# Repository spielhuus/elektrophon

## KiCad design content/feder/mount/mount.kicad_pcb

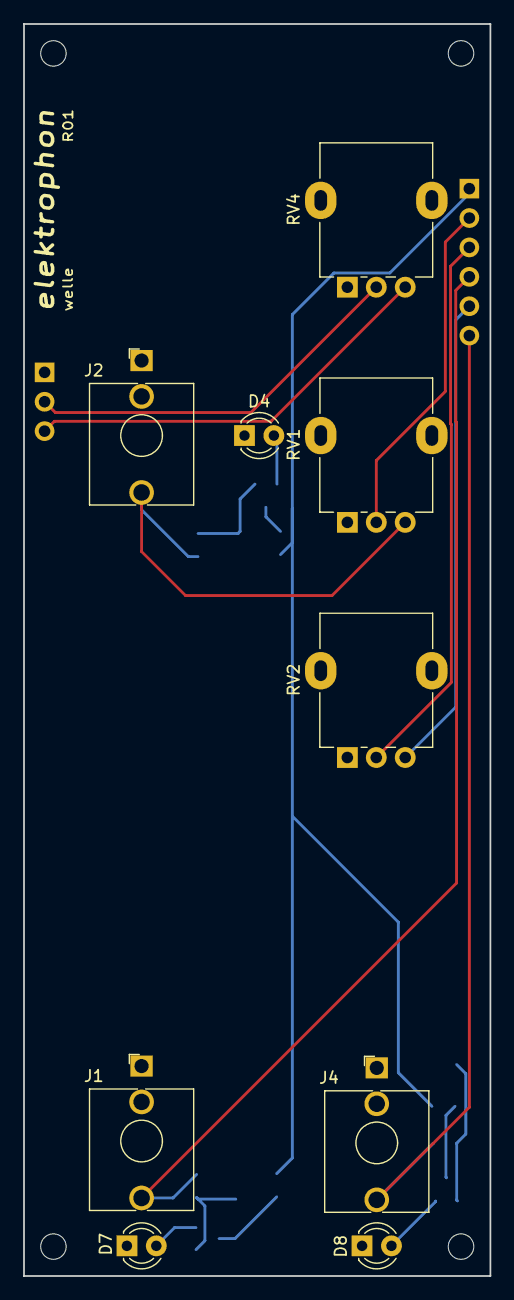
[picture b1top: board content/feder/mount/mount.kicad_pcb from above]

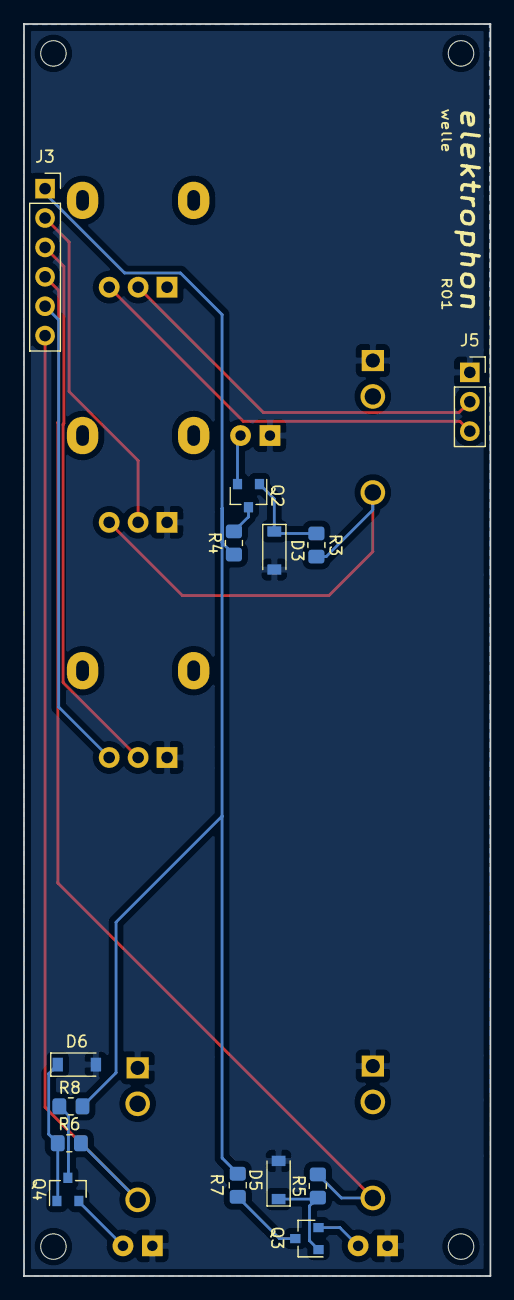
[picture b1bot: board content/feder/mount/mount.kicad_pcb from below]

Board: 2 copper layers, 40.3 x 108.2 mm, 27 parts (14 on the bottom side), 19 nets.

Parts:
D3, D5, D6: 1N4148W; D_SOD-123
D4: LED (Yellow); LED_D3.0mm
D7: LED (Green); LED_D3.0mm
D8: LED (Red); LED_D3.0mm
H1, H2, H3, H4: MountingHole; MountingHole_2.2mm_M2
J1: INPUT; Jack_3.5mm_WQP-PJ398SM_Vertical
J2: Control; Jack_3.5mm_WQP-PJ398SM_Vertical
J3: Conn_01x06_Male; PinSocket_1x06_P2.54mm_Vertical
J4: OUT; Jack_3.5mm_WQP-PJ398SM_Vertical
J5: Conn_01x03_Male; PinSocket_1x03_P2.54mm_Vertical
Q2, Q3, Q4: MMBT3904; SOT-23
R3, R5, R6: 100k; R_0805_2012Metric_Pad1.20x1.40mm_HandSolder
R4, R7, R8: 5k; R_0805_2012Metric_Pad1.20x1.40mm_HandSolder
RV1, RV2: 100k; Potentiometer_Alpha_RD901F-40-00D_Single_Vertical
RV4: 47k; Potentiometer_Alpha_RD901F-40-00D_Single_Vertical

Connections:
+5V: J3.1, R4.1, R7.1, R8.1
+15V: J3.5, RV2.3
/control: J3.2, RV1.2
/control_in: J2.T, R3.2, RV1.3
/input: J1.T, J3.4, R5.2
/out: J3.6, J4.T, R6.2
/range: J3.3, RV2.2
/shape_a: J5.2, RV4.2
/shape_b: J5.3, RV4.3
GND: D3.2, D4.1, D5.2, D6.2, D7.1, D8.1, J1.S, J2.S, J4.S, J5.1, RV1.1, RV2.1
unnamed: D3.1, Q2.1, R3.1
unnamed: D4.2, Q2.2
unnamed: D5.1, Q3.1, R5.1
unnamed: D6.1, Q4.1, R6.1
unnamed: D7.2, Q3.2
unnamed: D8.2, Q4.2
unnamed: Q2.3, R4.2
unnamed: Q3.3, R7.2
unnamed: Q4.3, R8.2

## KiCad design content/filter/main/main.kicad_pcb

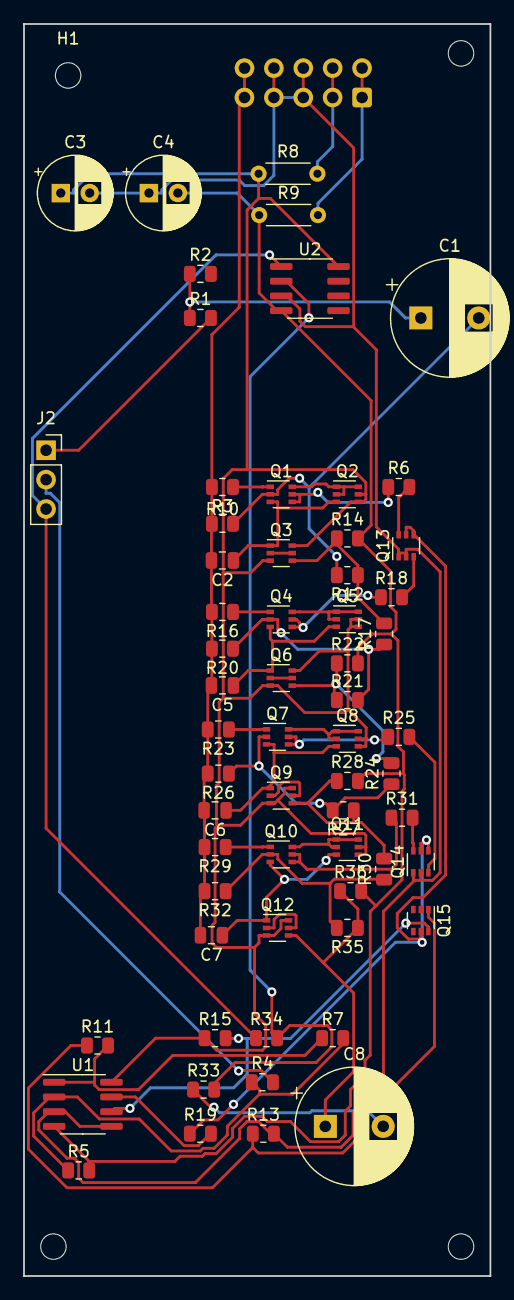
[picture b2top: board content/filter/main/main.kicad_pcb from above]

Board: 2 copper layers, 40.3 x 108.2 mm, 67 parts (1 on the bottom side), 50 nets.

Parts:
C1, C8: 10u; CP_Radial_D10.0mm_P5.00mm
C2, C5, C6, C7: 1n; C_0805_2012Metric
C3, C4: 22u; CP_Radial_D6.3mm_P2.50mm
H1, H2, H3, H4: MountingHole; MountingHole_2.2mm_M2
J1: 10 Pos; IDC-Header_2x05_P2.54mm_Vertical
J2: Conn_01x03_Female; PinSocket_1x03_P2.54mm_Vertical
Q1, Q3, Q4, Q6, Q7, Q9, Q10, Q12, Q13, Q14, Q15: DMMT3904W; SOT-363_SC-70-6
Q2, Q5, Q8, Q11: DMMT3906W; SOT-363_SC-70-6
R1, R2, R12, R14, R17, R21, R22, R24, R27, R28, R30, R33, R35, R36: 10k; R_0805_2012Metric
R3, R10, R16, R20, R23, R26, R29, R32: 220; R_0805_2012Metric
R4, R34: 100k; R_0805_2012Metric
R5: 200k; R_0805_2012Metric
R6, R13, R18, R25, R31: 1k; R_0805_2012Metric
R7: 51k; R_0805_2012Metric
R8, R9: 10; R_Axial_DIN0204_L3.6mm_D1.6mm_P5.08mm_Horizontal
R11: 27k; R_0805_2012Metric
R15: 1M; R_0805_2012Metric
R19: 2.2k; R_0805_2012Metric
U1, U2: TL072; SOIC-8_3.9x4.9mm_P1.27mm

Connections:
+5V: C2.2, C5.2, C6.2, C7.2, J1.9, J1.10, R3.2, R10.2, R16.2, R20.2, R23.2, R26.2, R29.2, R32.2
+15V: C3.1, Q2.4, Q2.5, Q3.3, Q3.6, Q5.4, Q5.5, Q6.3, Q6.6, Q8.4, Q8.5, Q9.3, Q9.6, Q11.4, Q11.5, Q12.3, Q12.6, R8.1, R15.1, U1.8, U2.8
-15V: C4.2, R5.2, R9.1, R14.2, R22.2, R28.2, R36.2, U1.4, U2.4
/CV: J2.2, R4.2
/IN: J2.1, R1.2
/OUT: J2.3, R34.1, U2.1
GND: C3.2, C4.1, J1.5, J1.6, J1.7, J1.8, Q13.1, Q13.2, Q14.1, Q14.2, R13.2, U1.3, U1.5, U2.3
unnamed: C1.1, R1.1, R2.1
unnamed: C1.2, Q1.2, R10.1, R12.2
unnamed: C2.1, Q1.3, Q2.3, Q3.1
unnamed: C5.1, Q4.3, Q5.3, Q6.1
unnamed: C6.1, Q7.3, Q8.3, Q9.1
unnamed: C7.1, Q10.3, Q11.3, Q12.1
unnamed: C8.1, Q12.4, R35.1, R36.1
unnamed: C8.2, R33.1
unnamed: Q1.1, R3.1
unnamed: Q1.4, Q1.5, R6.1
unnamed: Q1.6, Q2.1, Q2.2, Q2.6
unnamed: Q3.2, Q3.5
unnamed: Q3.4, R12.1, R14.1, R17.2
unnamed: Q4.1, R16.1
unnamed: Q4.2, R17.1, R20.1, R21.2
unnamed: Q4.4, Q4.5, R18.1
unnamed: Q4.6, Q5.1, Q5.2, Q5.6
unnamed: Q6.2, Q6.5
unnamed: Q6.4, R21.1, R22.1, R24.2
unnamed: Q7.1, R23.1
unnamed: Q7.2, R24.1, R26.1, R27.2
unnamed: Q7.4, Q7.5, R25.1
unnamed: Q7.6, Q8.1, Q8.2, Q8.6
unnamed: Q9.2, Q9.5
unnamed: Q9.4, R27.1, R28.1, R30.2
unnamed: Q10.1, R29.1
unnamed: Q10.2, R30.1, R32.1, R35.2
unnamed: Q10.4, Q10.5, R31.1
unnamed: Q10.6, Q11.1, Q11.2, Q11.6
unnamed: Q12.2, Q12.5
unnamed: Q13.3, R18.2
unnamed: Q13.4, Q13.5, Q14.4, Q14.5, Q15.5, R19.1
unnamed: Q13.6, R6.2
unnamed: Q14.3, R25.2
unnamed: Q14.6, R31.2
unnamed: Q15.1, R11.1, R13.1
unnamed: Q15.6, R15.2, U1.6
unnamed: R4.1, R5.1, R7.2, U1.2
unnamed: R7.1, R11.2, U1.1
unnamed: R19.2, U1.7
unnamed: R33.2, R34.2, U2.2
VN: J1.1, J1.2, R9.2
VP: J1.3, J1.4, R8.2

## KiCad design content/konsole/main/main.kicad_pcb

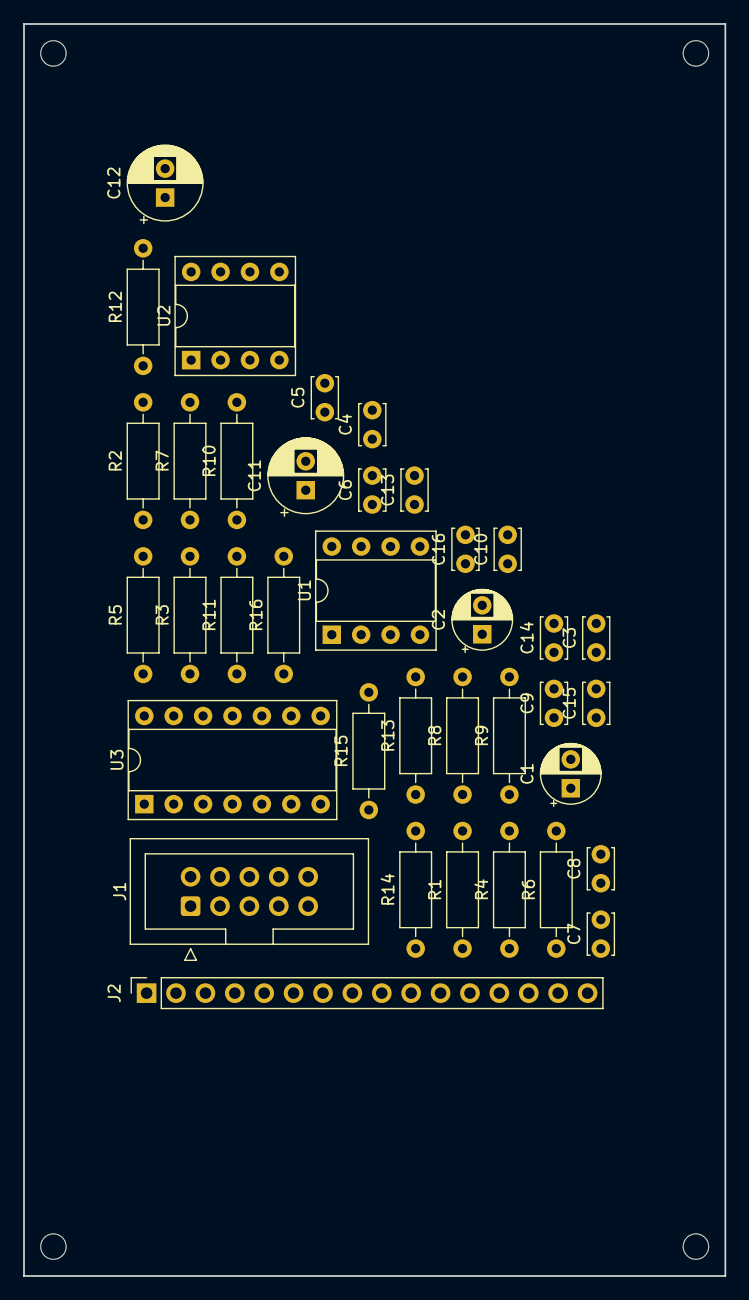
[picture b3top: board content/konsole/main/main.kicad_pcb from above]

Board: 2 copper layers, 60.6 x 108.2 mm, 41 parts (0 on the bottom side), 22 nets, no tracks yet.

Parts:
C1, C2: 10u; CP_Radial_D5.0mm_P2.50mm
C3, C4: 4u7; C_Disc_D3.4mm_W2.1mm_P2.50mm
C5, C6: 47p; C_Disc_D3.4mm_W2.1mm_P2.50mm
C7, C8, C9, C10, C13, C14, C15, C16: 0.1u; C_Disc_D3.4mm_W2.1mm_P2.50mm
C11, C12: 22u; CP_Radial_D6.3mm_P2.50mm
H1, H2, H3, H4: MountingHole; MountingHole_2.2mm_M2
J1: IDC Header; IDC-Header_2x05_P2.54mm_Vertical
J2: Conn_01x16_Female; PinSocket_1x16_P2.54mm_Vertical
R1, R2, R5, R6, R13, R14: 5k; R_Axial_DIN0207_L6.3mm_D2.5mm_P10.16mm_Horizontal
R3, R4, R9, R10, R15, R16: 10k; R_Axial_DIN0207_L6.3mm_D2.5mm_P10.16mm_Horizontal
R7, R8: 1k; R_Axial_DIN0207_L6.3mm_D2.5mm_P10.16mm_Horizontal
R11, R12: 10; R_Axial_DIN0207_L6.3mm_D2.5mm_P10.16mm_Horizontal
U1, U2: NE5532; DIP-8_W7.62mm_Socket
U3: TL074; DIP-14_W7.62mm_Socket

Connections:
+5V: J1.9, J1.10
+15V: C1.1, C7.1, C9.1, C11.1, C13.1, C15.1, C16.1, J2.15, R11.1, U1.8, U2.8, U3.4
-15V: C2.2, C8.2, C10.2, C12.2, C14.2, R12.1, U1.4, U2.4, U3.11
/LEFT: C5.2, J2.1, R3.2, U1.2
/LEFT_OUT: C3.1, R15.1, U1.7
/RIGHT: C6.2, J2.2, R4.2, U2.2
/RIGHT_OUT: C4.1, R16.1, U2.7
/STEREO_L: J2.4, R7.1
/STEREO_R: J2.3, R8.1
GND: C1.2, C2.1, C7.2, C8.1, C9.2, C10.1, C11.2, C12.1, C13.2, C14.1, C15.2, C16.2, J1.5, J1.6, J1.7, J1.8, J2.16, R1.2, R2.2, R5.2, R6.2, R13.2, R14.2
unnamed: C3.2, R5.1, R7.2
unnamed: C4.2, R6.1, R8.2
unnamed: C5.1, R3.1, R9.2, U1.1
unnamed: C6.1, R4.1, R10.2, U2.1
unnamed: R1.1, U1.3
unnamed: R2.1, U2.3
unnamed: R10.1, R16.2, U2.6
unnamed: R13.1, U1.5
unnamed: R14.1, U2.5
unnamed: R9.1, R15.2, U1.6
VN: J1.1, J1.2, R12.2
VP: J1.3, J1.4, R11.2

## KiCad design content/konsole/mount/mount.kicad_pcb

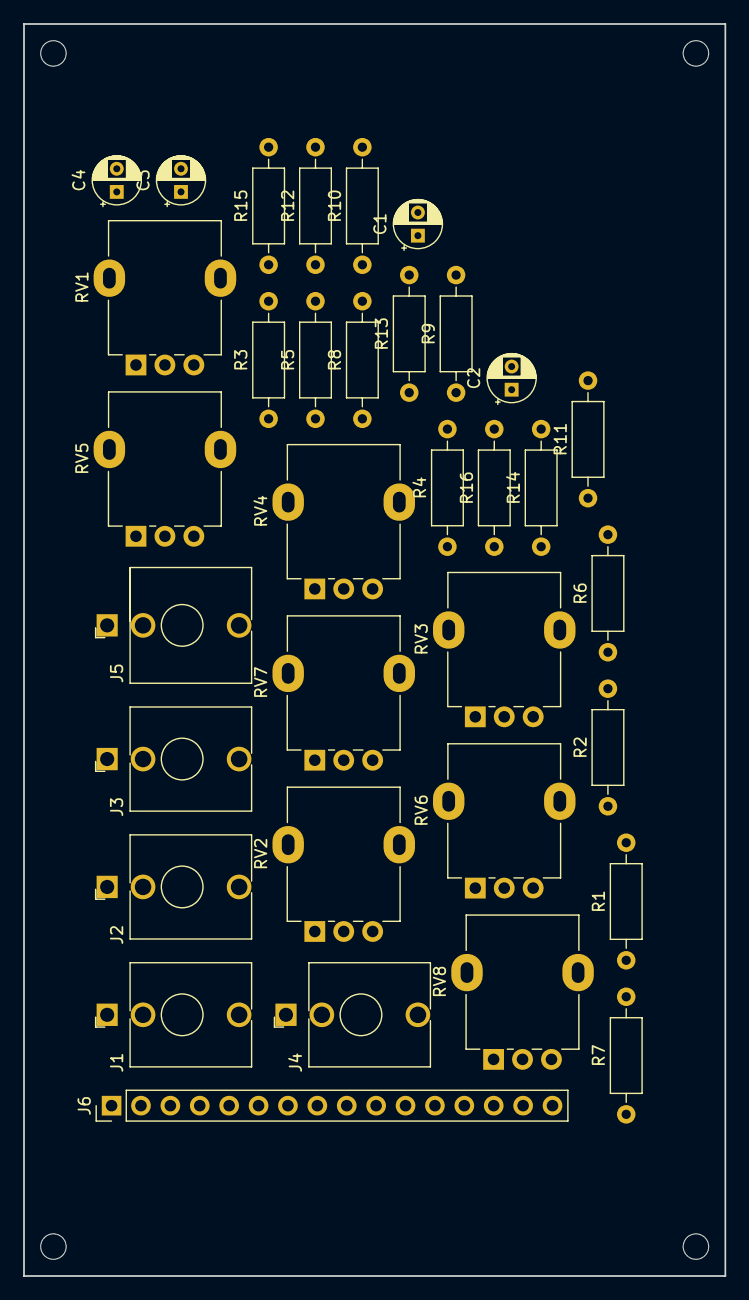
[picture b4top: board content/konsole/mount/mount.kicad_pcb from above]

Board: 2 copper layers, 60.6 x 108.2 mm, 38 parts (0 on the bottom side), 25 nets, no tracks yet.

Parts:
C1, C2, C3, C4: 4u7; CP_Radial_D4.0mm_P2.00mm
H1, H2, H3, H4: MountingHole; MountingHole_2.2mm_M2
J1: #1; Jack_3.5mm_WQP-PJ398SM_Vertical
J2: #2; Jack_3.5mm_WQP-PJ398SM_Vertical
J3: #3; Jack_3.5mm_WQP-PJ398SM_Vertical
J4: #4; Jack_3.5mm_WQP-PJ398SM_Vertical
J5: STEREO_OUT; Jack_3.5mm_WQP-PJ301BM_Vertical
J6: Conn_01x16_Male; PinHeader_1x16_P2.54mm_Vertical
R1, R2, R3, R4, R5, R6, R7, R8, R9, R10, R11, R12, R13, R14, R15, R16: 10k; R_Axial_DIN0207_L6.3mm_D2.5mm_P10.16mm_Horizontal
RV1, RV2, RV3, RV4: 10k LOG; Potentiometer_Alpha_RD901F-40-00D_Single_Vertical
RV5, RV6, RV7, RV8: 25k; Potentiometer_Alpha_RD901F-40-00D_Single_Vertical

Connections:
/LEFT: J6.2, R9.1, R11.1, R13.1, R15.1
/RIGHT: J6.1, R10.2, R12.2, R14.2, R16.2
/STEREO_L: J5.R, J6.4
/STEREO_R: J5.T, J6.3
GND: J1.S, J2.S, J3.S, J4.S, J5.S, J6.16, RV1.3, RV2.3, RV3.3, RV4.3, RV5.2, RV6.2, RV7.2, RV8.2
unnamed: C1.1, RV1.2
unnamed: C1.2, R1.2, R2.2
unnamed: C2.1, RV2.2
unnamed: C2.2, R3.2, R4.2
unnamed: C3.1, RV3.2
unnamed: C3.2, R5.2, R6.2
unnamed: C4.1, RV4.2
unnamed: C4.2, R7.2, R8.2
unnamed: J1.T, RV1.1
unnamed: J2.T, RV2.1
unnamed: J3.T, RV3.1
unnamed: J4.T, RV4.1
unnamed: R1.1, R9.2, RV5.1
unnamed: R2.1, R10.1, RV5.3
unnamed: R3.1, R11.2, RV6.1
unnamed: R4.1, R12.1, RV6.3
unnamed: R5.1, R13.2, RV7.1
unnamed: R6.1, R14.1, RV7.3
unnamed: R7.1, R15.2, RV8.1
unnamed: R8.1, R16.1, RV8.3

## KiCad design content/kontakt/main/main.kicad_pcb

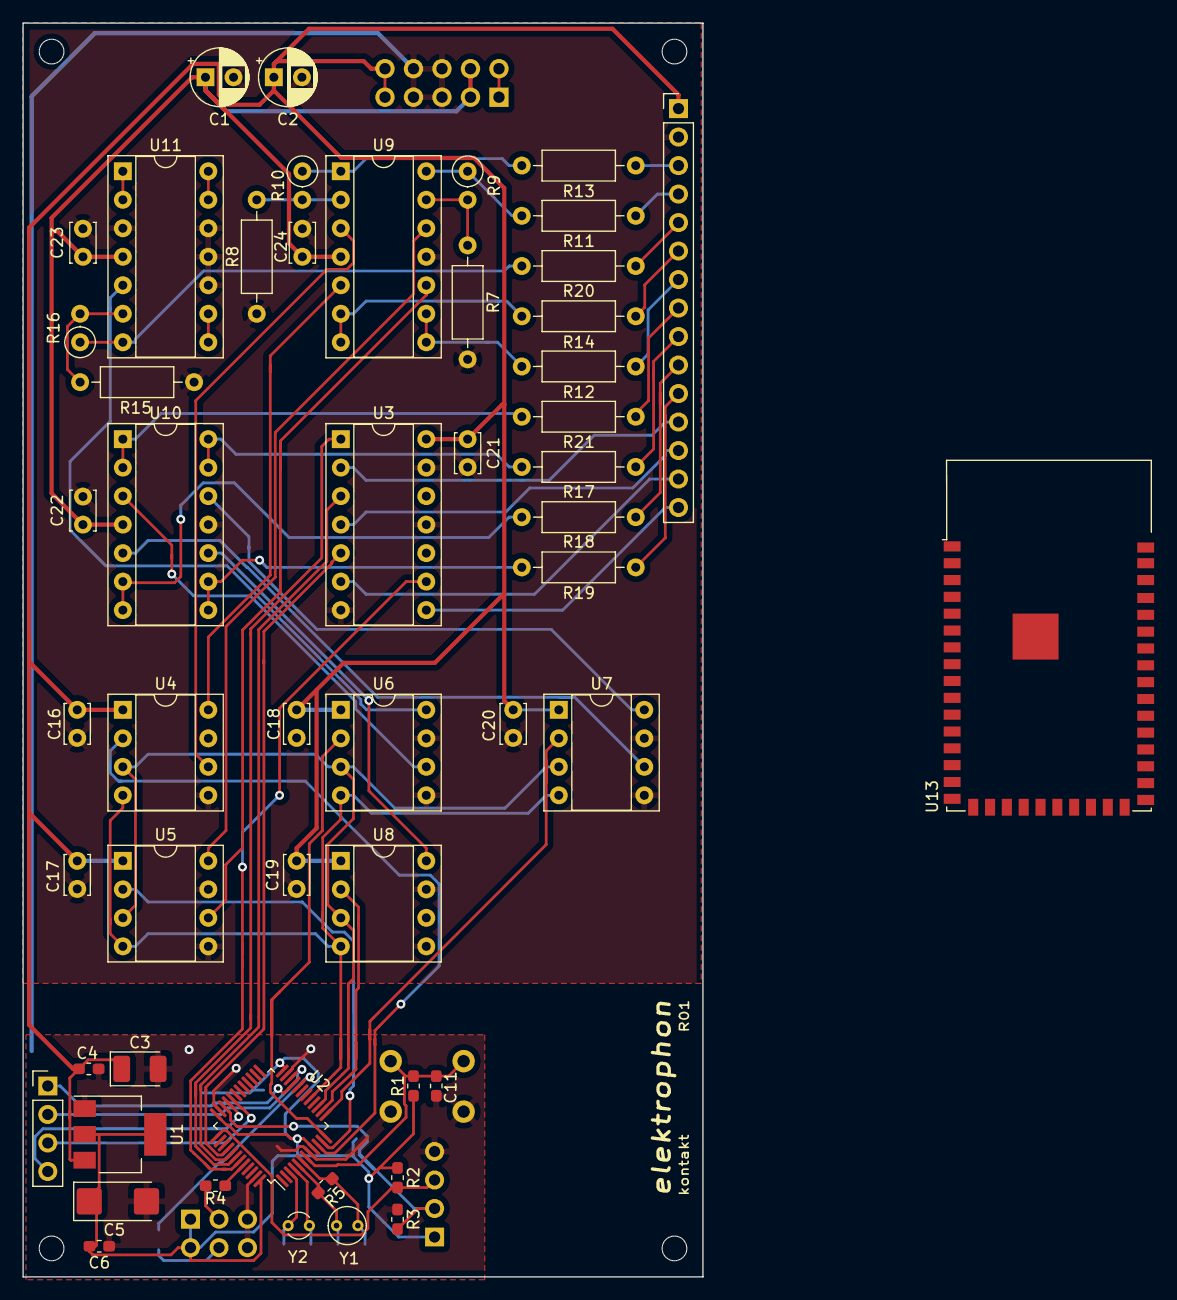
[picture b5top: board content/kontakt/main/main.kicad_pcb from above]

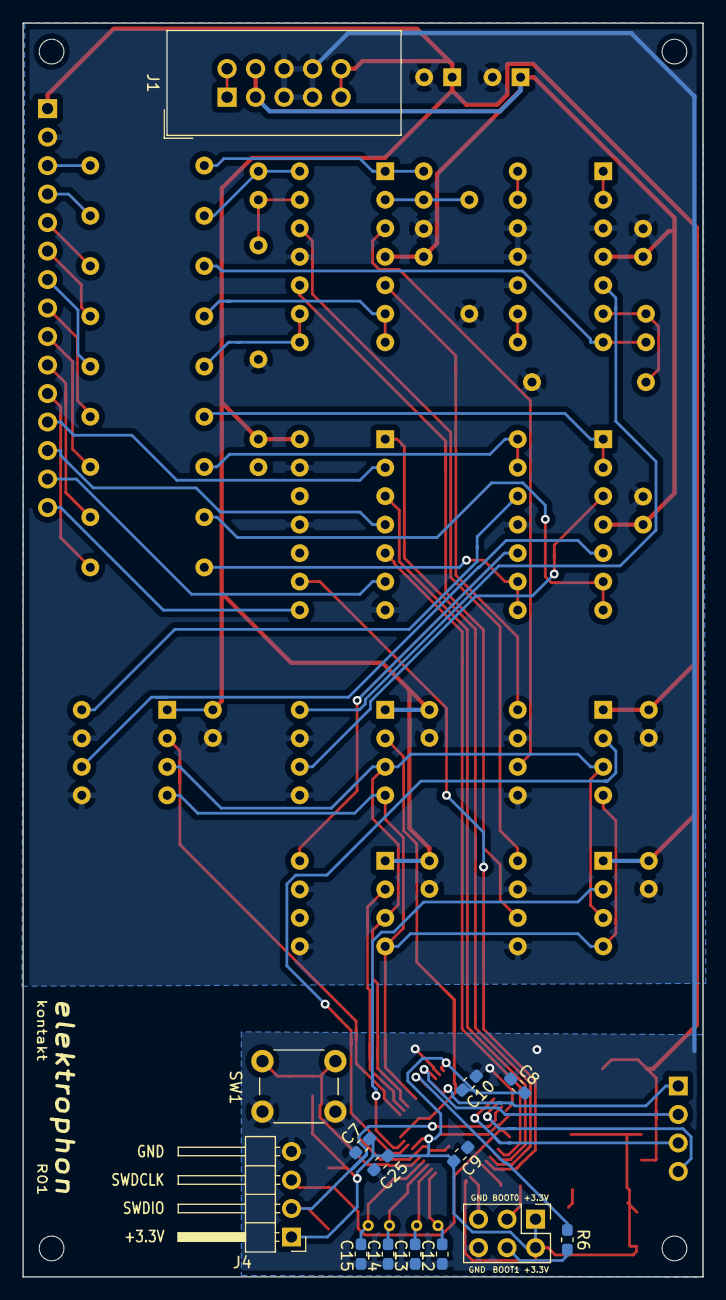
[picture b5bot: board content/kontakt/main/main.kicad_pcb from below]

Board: 2 copper layers, 60.6 x 111.8 mm, 70 parts (14 on the bottom side), 69 nets.

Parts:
C1, C2: 10u; CP_Radial_D5.0mm_P2.50mm
C3: 100u; CP_EIA-3528-15_AVX-H_Pad1.50x2.35mm_HandSolder
C4, C6, C8, C9, C10, C11: 100n; C_0603_1608Metric_Pad1.05x0.95mm_HandSolder
C5: 330u; CP_EIA-6032-20_AVX-F_Pad2.25x2.35mm_HandSolder
C7: 10n; C_0603_1608Metric_Pad1.05x0.95mm_HandSolder
C12, C13, C14, C15: 20p; C_0603_1608Metric_Pad1.05x0.95mm_HandSolder
C16, C17, C18, C19, C20, C21, C22, C23, C24: 0.1u; C_Disc_D3.4mm_W2.1mm_P2.50mm
C25: 1u; C_0603_1608Metric_Pad1.05x0.95mm_HandSolder
H1, H2, H3, H4: MountingHole; MountingHole_2.2mm_M2
J1: IDC Header; IDC-Header_2x05_P2.54mm_Vertical
J2: Conn_01x15_Female; PinHeader_1x15_P2.54mm_Vertical
J3: Conn_01x04_Female; PinHeader_1x04_P2.54mm_Vertical
J4: SWD; PinHeader_1x04_P2.54mm_Horizontal
J5: Conn_02x03_Odd_Even; PinHeader_2x03_P2.54mm_Vertical
R1, R2, R3: 10k; R_0603_1608Metric_Pad1.05x0.95mm_HandSolder
R4, R6: 100k; R_0603_1608Metric_Pad1.05x0.95mm_HandSolder
R5: 1M; R_0603_1608Metric_Pad1.05x0.95mm_HandSolder
R7, R8, R15: 22k; R_Axial_DIN0207_L6.3mm_D2.5mm_P10.16mm_Horizontal
R9, R10, R16: 17k; R_Axial_DIN0207_L6.3mm_D2.5mm_P2.54mm_Vertical
R11, R12, R13, R14, R17, R18, R19, R20, R21: 1k; R_Axial_DIN0207_L6.3mm_D2.5mm_P10.16mm_Horizontal
SW1: SW_Push; SW_PUSH_6mm
U1: AMS1117-3.3; SOT-223-3_TabPin2
U2: STM32F103C8Tx; LQFP-48_7x7mm_P0.5mm
U3: 40106; DIP-14_W7.62mm_Socket
U4, U5, U6, U7, U8: MCP4822; DIP-8_W7.62mm_Socket
U9, U10, U11: LM324; DIP-14_W7.62mm_Socket
U13: ESP32-S2-WROVER
Y1: 8MHz; Crystal_Round_D3.0mm_Vertical
Y2: 32.768K; Crystal_Round_D2.0mm_Vertical

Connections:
+3V3: C5.1, C6.2, C7.2, C8.2, C9.2, C10.2, C25.2, J4.1, J5.1, J5.2, R1.2, R2.1, U1.2, U2.9, U2.24, U2.36, U2.48
+5V: C2.1, C3.1, C4.2, C16.1, C17.1, C18.1, C19.1, C20.1, C21.1, J1.9, J1.10, J2.1, U1.3, U3.14, U4.1, U5.1, U6.1, U7.1, U8.1
+15V: C1.1, C22.1, C23.1, C24.1, J1.3, J1.4, U9.4, U10.4, U11.4
-15V: J1.1, J1.2
/Analog Circuit/SIG_NOTE_1: U4.6, U9.3
/Analog Circuit/SIG_NOTE_2: U5.8, U9.12
/Analog Circuit/SIG_NOTE_3: U6.8, U11.5
/Analog Circuit/SIG_PITCH_BEND_1: U7.8, U10.12
/Analog Circuit/SIG_PITCH_BEND_2: U7.6, U10.5
/Analog Circuit/SIG_PITCH_BEND_3: U8.8, U10.10
/Analog Circuit/SIG_VELOCITY_1: U4.8, U9.5
/Analog Circuit/SIG_VELOCITY_2: U5.6, U9.10
/Analog Circuit/SIG_VELOCITY_3: U6.6, U10.3
/STM32 Board/BOOT0: R4.1, U2.44
/STM32 Board/BOOT1: R6.1, U2.20
/STM32 Board/OSCIN: C14.1, R5.1, U2.5, Y1.1
/STM32 Board/OSCOUT: C15.1, R5.2, U2.6, Y1.2
/STM32 Board/PC14: C12.1, U2.3, Y2.1
/STM32 Board/PC15: C13.1, U2.4, Y2.2
/STM32 Board/RESET: C11.2, R1.1, SW1.2, U2.7
/STM32 Board/SWDCLK: J4.3, R2.2, U2.37
/STM32 Board/SWDIO: J4.2, R3.2, U2.34
CS_1: U2.10, U4.2
CS_2: U2.11, U5.2
CS_3: U2.12, U6.2
CS_4: U2.13, U7.2
CS_5: U2.14, U8.2
GND: C1.2, C2.2, C3.2, C4.1, C5.2, C6.1, C7.1, C8.1, C9.1, C10.1, C11.1, C12.2, C13.2, C14.2, C15.2, C16.2, C17.2, C18.2, C19.2, C20.2, C21.2, C22.2, C23.2, C24.2, C25.1, J1.5, J1.6, J1.7, J1.8, J2.2, J4.4, J5.5, J5.6, R3.1, R7.1, R8.1, R15.1, SW1.1, U1.1, U2.8, U2.23, U2.35, U2.47, U3.7, U3.11, U3.13, U4.5, U4.7, U5.5, U5.7, U6.5, U6.7, U7.5, U7.7, U8.5, U8.7, U9.11, U10.11, U11.3, U11.10, U11.11, U11.12
LED_ACTIVITY: J3.1, U2.21
LED_CONNECT: J3.2, U2.22
MOSI: U2.17, U4.4, U5.4, U6.4, U7.4, U8.4
unnamed: J5.3, R4.2
unnamed: J5.4, R6.2
unnamed: R7.2, R9.2, U9.13
unnamed: R10.1, R13.2, U9.1
unnamed: R8.2, R10.2, U9.2
unnamed: R9.1, R11.2, U9.14
unnamed: R12.2, U9.8, U9.9
unnamed: R14.2, U9.6, U9.7
unnamed: R15.2, R16.2, U11.6
unnamed: R16.1, R20.2, U11.7
unnamed: R17.2, U10.13, U10.14
unnamed: R18.2, U10.6, U10.7
unnamed: R19.2, U10.8, U10.9
unnamed: R21.2, U10.1, U10.2
unnamed: U11.1, U11.2
unnamed: U11.8, U11.9
unnamed: U11.13, U11.14
unnamed: U13.1, U13.26, U13.42, U13.43
Note_1: J2.3, R13.1
Note_2: J2.4, R11.1
Note_3: J2.5, R20.1
OUT_CLOCK: J2.15, U3.8
OUT_TRIGGER_1: J2.12, U3.2
OUT_TRIGGER_2: J2.13, U3.4
OUT_TRIGGER_3: J2.14, U3.6
PA11: J3.3, U2.32
PA12: J3.4, U2.33
PITCH_BEND_1: J2.9, R17.1
PITCH_BEND_2: J2.10, R18.1
PITCH_BEND_3: J2.11, R19.1
SCK: U2.15, U4.3, U5.3, U6.3, U7.3, U8.3
SIG_CLOCK: U2.43, U3.9
SIG_TRIGGER_1: U2.42, U3.1
SIG_TRIGGER_2: U2.41, U3.3
SIG_TRIGGER_3: U2.40, U3.5
Velocity_1: J2.6, R14.1
Velocity_2: J2.7, R12.1
Velocity_3: J2.8, R21.1

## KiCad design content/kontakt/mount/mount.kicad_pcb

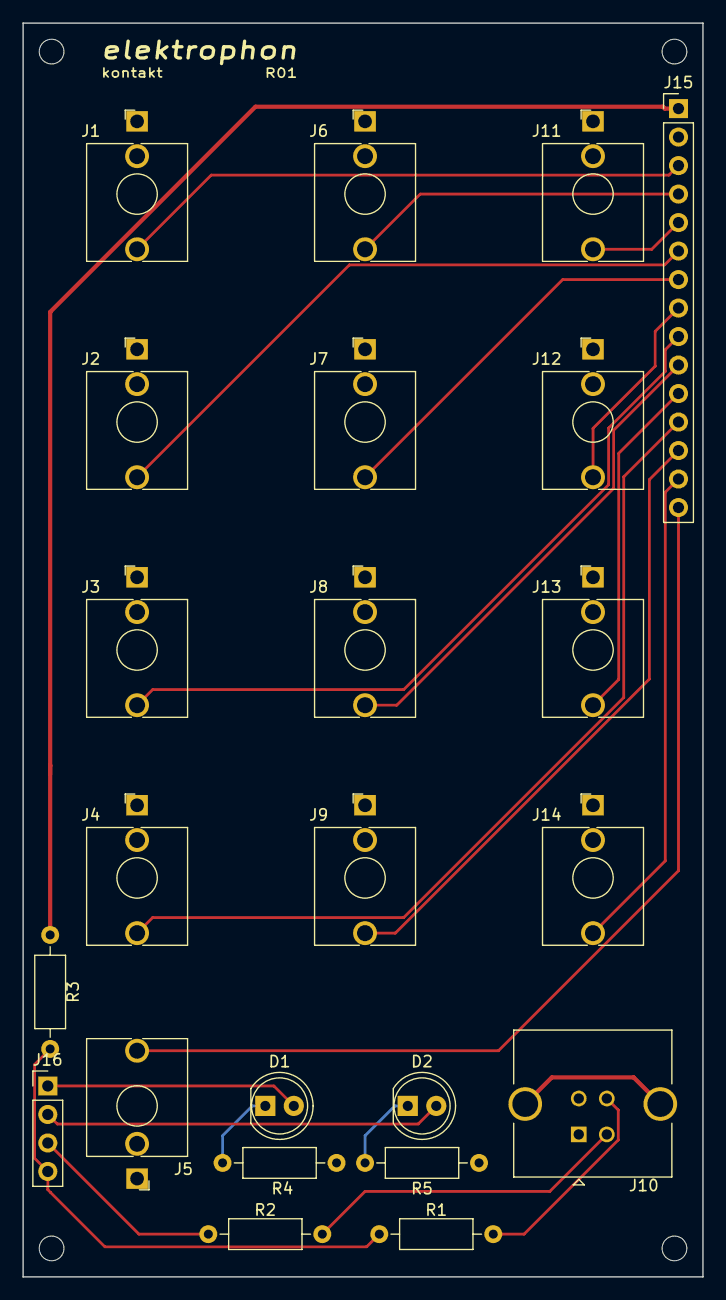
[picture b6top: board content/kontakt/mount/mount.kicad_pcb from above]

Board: 2 copper layers, 60.6 x 111.8 mm, 27 parts (0 on the bottom side), 23 nets.

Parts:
D1, D2: LED; LED_D5.0mm
H1, H2, H3, H4: MountingHole; MountingHole_2.2mm_M2
J1, J2, J3, J4, J5, J6, J7, J8, J9, J11, J12, J13, J14: INPUT; Jack_3.5mm_WQP-PJ398SM_Vertical
J10: USB_B; USB_B_TE_5787834_Vertical
J15: Conn_01x15_Male; PinHeader_1x15_P2.54mm_Vertical
J16: Conn_01x04_Male; PinHeader_1x04_P2.54mm_Vertical
R1, R2: 20; R_Axial_DIN0207_L6.3mm_D2.5mm_P10.16mm_Horizontal
R3: 1k5; R_Axial_DIN0207_L6.3mm_D2.5mm_P10.16mm_Horizontal
R4, R5: 56; R_Axial_DIN0207_L6.3mm_D2.5mm_P10.16mm_Horizontal

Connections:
+5V: J15.1, R3.2
/PA11: J16.3, R2.1
/PA12: J16.4, R1.1, R3.1
GND: J1.S, J2.S, J3.S, J4.S, J5.S, J6.S, J7.S, J8.S, J9.S, J10.4, J11.S, J12.S, J13.S, J14.S, J15.2, R4.2, R5.2
LED_ACTIVITY: D1.2, J16.1
LED_CONNECT: D2.2, J16.2
unnamed: D1.1, R4.1
unnamed: D2.1, R5.1
unnamed: J10.2, R2.2
unnamed: J10.3, R1.2
Note_1: J1.T, J15.3
Note_2: J6.T, J15.4
Note_3: J11.T, J15.5
OUT_CLOCK: J5.T, J15.15
OUT_TRIGGER_1: J4.T, J15.12
OUT_TRIGGER_2: J9.T, J15.13
OUT_TRIGGER_3: J14.T, J15.14
PITCH_BEND_1: J3.T, J15.9
PITCH_BEND_2: J8.T, J15.10
PITCH_BEND_3: J13.T, J15.11
Velocity_1: J2.T, J15.6
Velocity_2: J7.T, J15.7
Velocity_3: J12.T, J15.8

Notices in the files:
content/feder/mount/mount.kicad_pcb:
License CC BY 4.0 - Attribution 4.0 International
